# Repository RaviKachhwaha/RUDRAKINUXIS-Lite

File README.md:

<h1 align="center">
  <br>

  <br>
  RUDRAKINUXIS-Lite
  <br>
</h1>
<h3 align="center">
A fully open-sourced complete Field Oriented Control ESC. 
</h3>

| Front Render | Back Render | 
| --- | --- |
|  |  | 

## Schematics  

Here are the schematic design,

## Features
- **STM32G431CBU6 MCU** - Arm Cortex-M4 with CORDIC accelerator, running at 170 MHz.
- **A 24kHz 6S FOC motor controller and real-time DSP**.
- **Texas Instruments DRV8300 gate driver**.
- **600W continuous with 16 AWG bus wire and 2oz copper support**.
- Power and arming status indicator LEDs.
- High-speed CAN FD and DShot support.
- **USB C** - for flashing and telemetry.
- A 20-25.2V (6S LiPo) pad input for power.
- **3-phase 0.5mΩ low side shunts** - with dedicated Kelvin differential sensing.
- **LMR36510 synchronous buck converter** - high efficiency step down for the 10V gate rail.
- **AP2112K ultra low noise 3.3V LDO** - delivers clean, ripple free power to the MCU ADC.
- **Phase BEMF and bus voltage sensing** - for sensorless motor tracking and battery telemetry.
- **Onboard NTC thermistor** - for real time thermal monitoring and overheat protection.
- **USBLC6-2SC6 ESD protection** - hardware transient voltage clamping on USB data lines.
- **SWD debug header** - 5-pin port for direct ST-Link firmware flashing and live debugging.

## PCB Design 
|  |
|--- |  

 ### The PCB is 4 layers with dimensions 78.5000 x 55.0000 mm, made to be easily useable for anyone.  

 ### All the PCB files are [here](https://github.com/RaviKachhwaha/RUDRAKINUXIS-Lite/blob/main/hardware) 

| Front Layer | Inner Layer 1 |
| --- | --- |
|  |  |
| Inner Layer 2 | Bottom layer |
|  |  |

## Pinout  

This is a general pinout 

|  | 
| --- | 

Note :- Sorry, I am not able to create it's Pinout image due to storage issues in my PC, but I will create and upload pinout image as soon as possible.

(Credits to KiCad EDA for KiCad 10, STMicroelectronics for the STM32G4 MCU, Texas Instruments for the DRV8300 gate driver, and Hack Club for funding to make this possible.)

(Thanks to hack Club for funding.) 

## Why was it made?  

While using the normal old ESC for my many projects and in some times need's, I realised it doesn't have Field Oriented Control and high power support and I couldn't use it for high power and control needed project, unfortunately I had to think to buy a different high power ESC then I see that those have high power but not Field Oriented Control support or many have Field Oriented Control but cost very high and not have my needed pins and full control over every thing and use very low price components which give low quality, but now I designed one with the simplicity of STM32G431CBU6 with being able to get best Field Oriented Control and fastest processing and control over every thing and also programming support in a same board with high quality Field Oriented Control for best flight and have too many features and this will make many things possible.

## How you can get one for yourself? 

That is pretty easy, you have all the files you will need in the production folder, order the development  
board from any PCB fab ( I chose Lion Circuits or PCB Power cause its cheap in India and has good quality and also made in India ) and BINGO! You will have it to use for any purpose you want!  

## How do you use it?  
You can use it as any normal ESC board but first want to flash the firmware which is given in firmware folder, for flashing first connect the ESC to your computer via USB-C. Open your flashing tool (STM32CubeProgrammer or stm32flash), select the CP2102N COM port, and click **Download / Flash**. The onboard auto-reset circuit automatically enters the STM32 system bootloader, flashes the binary, and boots directly into your firmware and you are good to go!
I have attached a simple firmware to start with prebuild firmware available in the firmware folder.  

## BOM  
|Name|Purpose          |Quantity|Total Cost (USD)|Link               |Distributor|
|----|-----------------|--------|----------------|-------------------|-----------|
|PCBA|Board and Assembly|4       |194.20         |[Lion Circuits](lioncircuits.com)|Lion Circuits     |
|Electronic Components|BOM Component Sourcing|4       |189.85           |[Lion Circuits](lioncircuits.com)|Lion Circuits     |
|GenX Lithium Ion Battery - 6S|Lithium Ion Battery - 21.6V 9000mAh and 13C is needed to test this ESC without this there is no option to test it. So this is must needed.|1       |111.11          |[GenX Lithium Ion Battery](https://genxbattery.com/shop/genx-molicel-21-6v-9000mah-13c-premium-lithium-ion-rechargeable-battery)|GenX     |
| | | Total | 495.16 |

LCSC & DigiKey BOM for the components on board is [here](https://github.com/RaviKachhwaha/RUDRAKINUXIS-Lite/blob/main/components_bom.csv)

!!Thanks to ALL!!

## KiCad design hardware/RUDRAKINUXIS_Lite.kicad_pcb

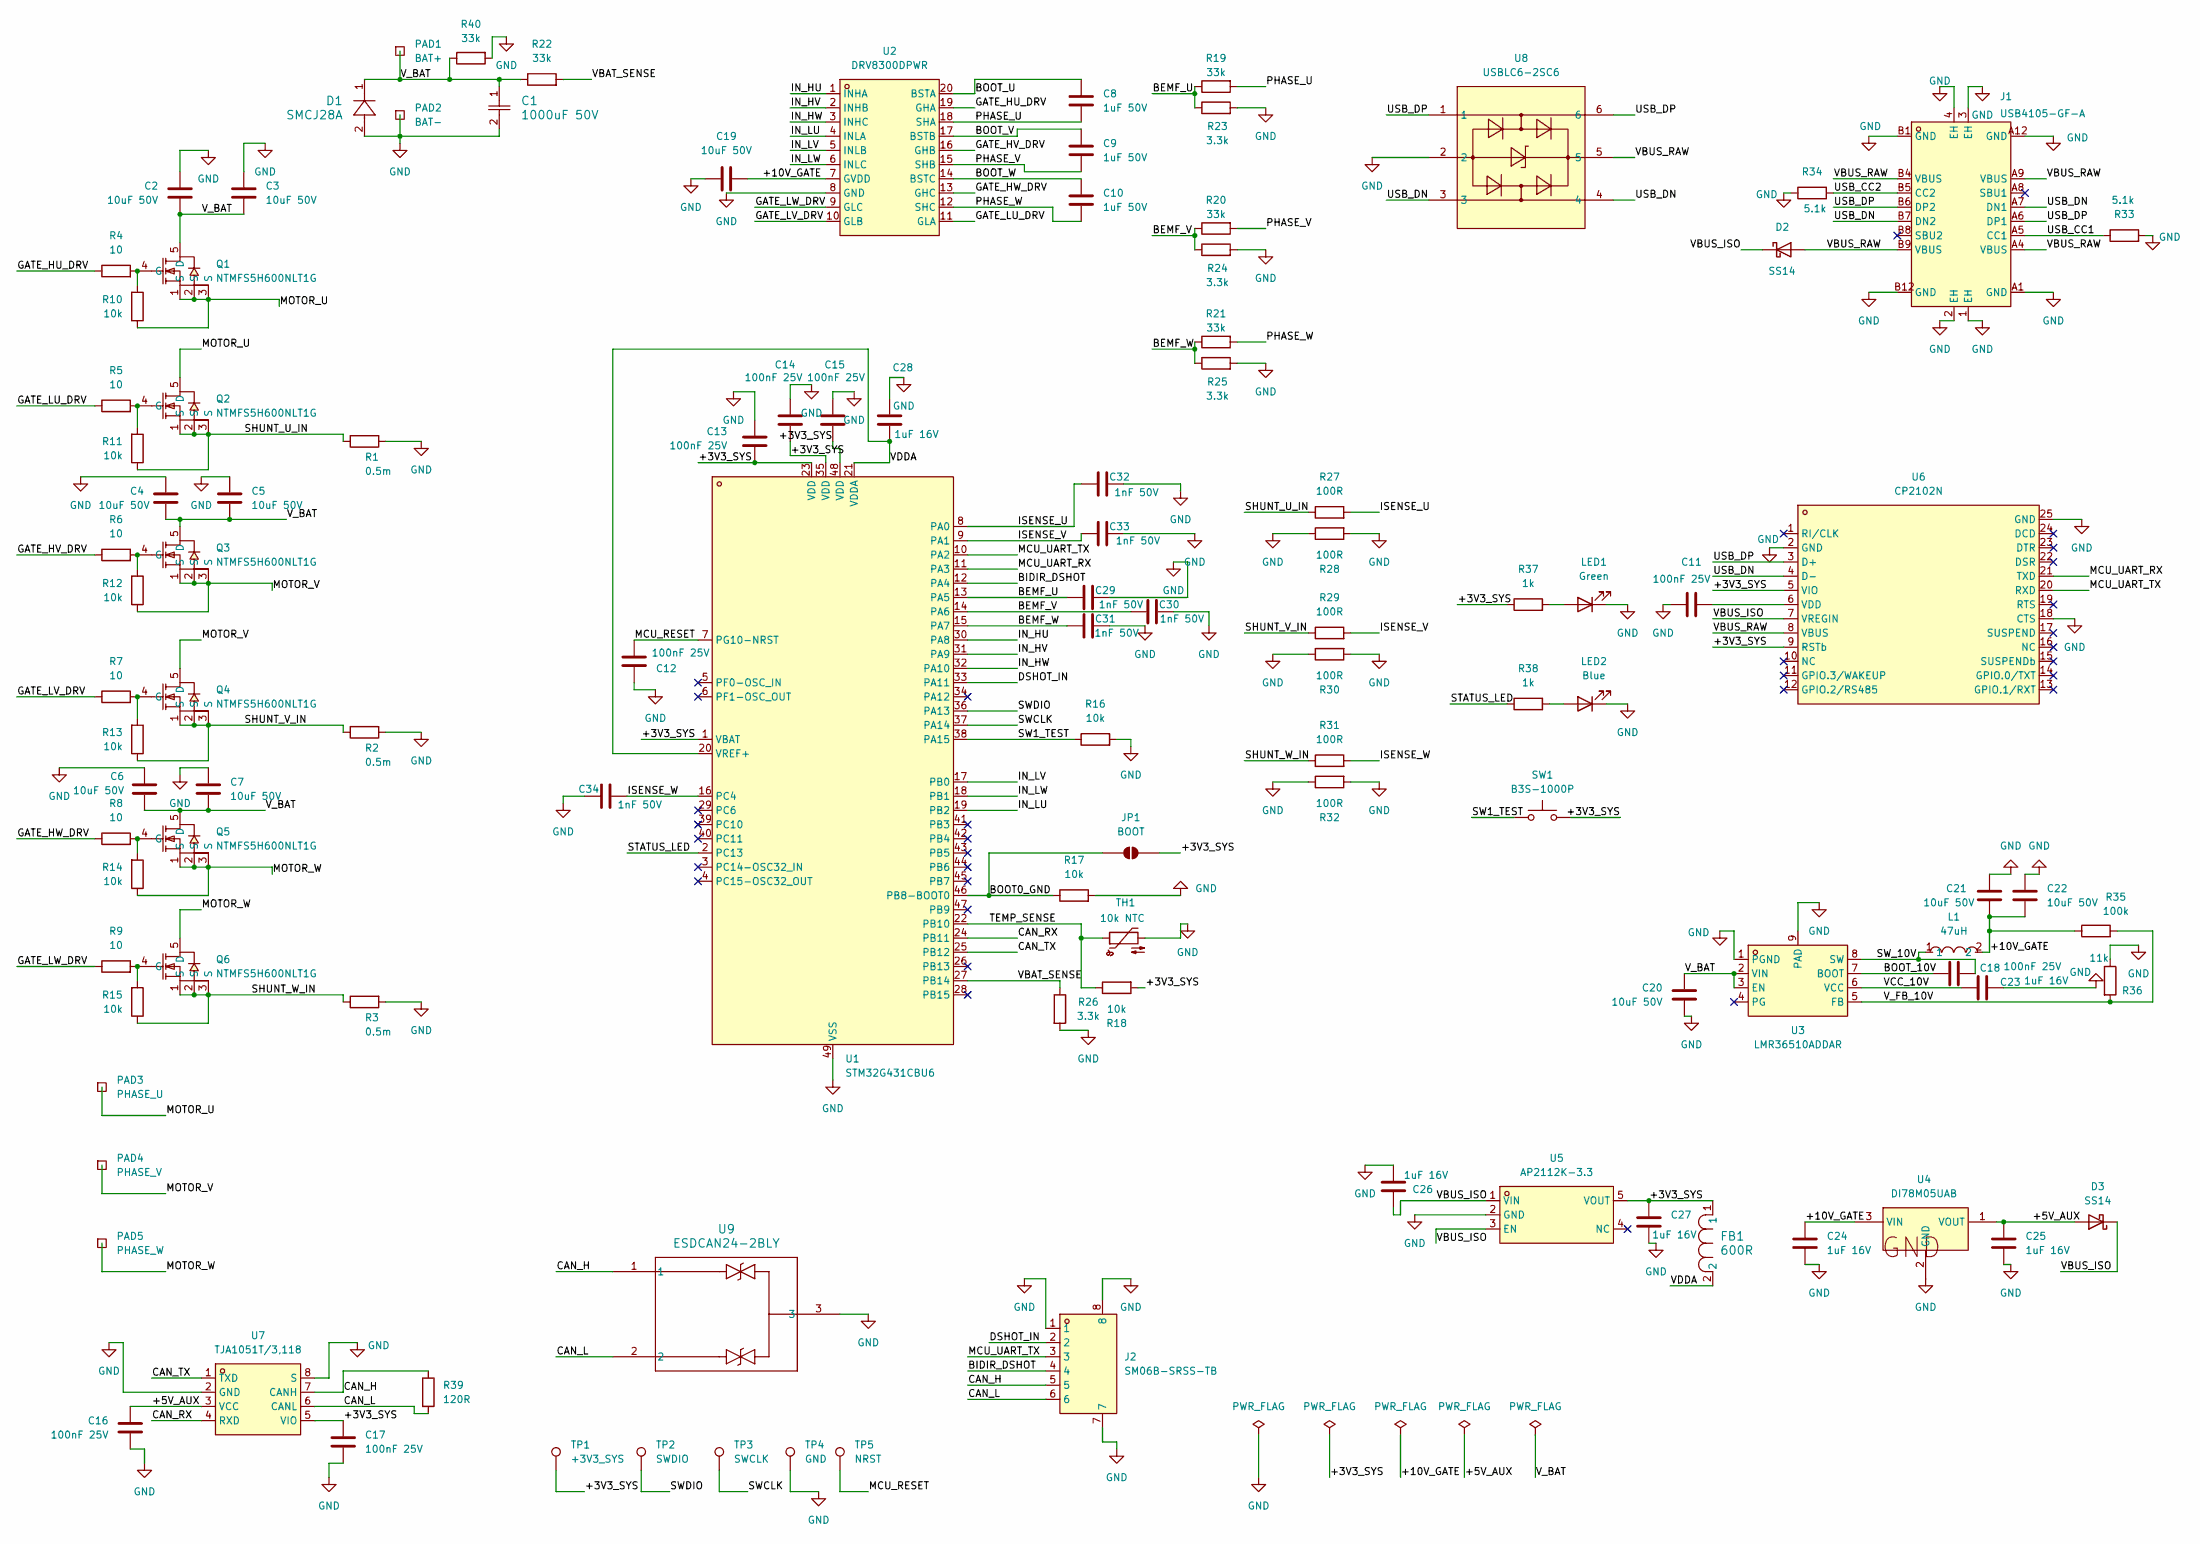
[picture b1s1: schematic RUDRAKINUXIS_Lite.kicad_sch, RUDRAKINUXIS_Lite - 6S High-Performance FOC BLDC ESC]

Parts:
C1: 1000uF 50V; CAP_16 X 25_PAN
C2, C3, C4, C5, C6, C7, C19, C20, C21, C22: 10uF 50V; C_1206_3216Metric
C8, C9, C10: 1uF 50V; C_0603_1608Metric
C11, C12, C13, C14, C15, C16, C17, C18: 100nF 25V; C_0603_1608Metric
C23, C24, C25, C26, C27, C28: 1uF 16V; C_0603_1608Metric
C29, C30, C31, C32, C33, C34: 1nF 50V; C_0603_1608Metric
D1: SMCJ28A; DIODE_DO-214AC
D2, D3: SS14; D_SMA
FB1: 600R; L_0603_1608Metric
J1: USB4105-GF-A; TYPE-C-SMD_SBC-160S1A-20-S412; MPN USB4105-GF-A; LCSC Part C3020560
J2: SM06B-SRSS-TB; CONN-SMD_SM06B-SRSS-TB-LF-SN; MPN SM06B-SRSS-TB(LF)(SN); LCSC Part C160405
JP1: BOOT; SolderJumper-2_P1.3mm_Open_RoundedPad1.0x1.5mm
L1: 47uH; IND-SMD_L10.2-W10.0; MPN CDRH105RNP-470NC; LCSC Part C225032
LED1: Green; LED_0603_1608Metric
LED2: Blue; LED_0603_1608Metric
PAD1: BAT+; TestPoint_THTPad_4.0x4.0mm_Drill2.0mm
PAD2: BAT-; TestPoint_THTPad_4.0x4.0mm_Drill2.0mm
PAD3: PHASE_U; TestPoint_THTPad_4.0x4.0mm_Drill2.0mm
PAD4: PHASE_V; TestPoint_THTPad_4.0x4.0mm_Drill2.0mm
PAD5: PHASE_W; TestPoint_THTPad_4.0x4.0mm_Drill2.0mm
Q1, Q2, Q3, Q4, Q5, Q6: NTMFS5H600NLT1G; DFN-5_L5.9-W4.9-P1.27-LS6.2-BL_CASE-488AA; MPN NTMFS5H600NLT1G; LCSC Part C463882
R1, R2, R3: 0.5m; R_2512_6332Metric
R4, R5, R6, R7, R8, R9: 10; R_0603_1608Metric
R10, R11, R12, R13, R14, R15, R16, R17, R18: 10k; R_0603_1608Metric
R19, R20, R21, R22: 33k; R_0603_1608Metric
R23, R24, R25, R26: 3.3k; R_0603_1608Metric
R27, R28, R29, R30, R31, R32: 100R; R_0603_1608Metric
R33, R34: 5.1k; R_0603_1608Metric
R35: 100k; R_0603_1608Metric
R36: 11k; R_0603_1608Metric
R37, R38: 1k; R_0603_1608Metric
R39: 120R; R_0805_2012Metric
R40: 33k; R_1206_3216Metric
SW1: B3S-1000P; SW_SPST_B3S-1000
TH1: 10k NTC; R_0603_1608Metric
TP1: +3V3_SYS; TestPoint_THTPad_2.0x2.0mm_Drill1.0mm
TP2: SWDIO; TestPoint_THTPad_2.0x2.0mm_Drill1.0mm
TP3: SWCLK; TestPoint_THTPad_2.0x2.0mm_Drill1.0mm
TP4: GND; TestPoint_THTPad_2.0x2.0mm_Drill1.0mm
TP5: NRST; TestPoint_THTPad_2.0x2.0mm_Drill1.0mm
U1: STM32G431CBU6; VQFN-48_L7.0-W7.0-P0.50-BL-EP5.5; MPN STM32G431CBU6; LCSC Part C529356
U2: DRV8300DPWR; TSSOP-20_L6.5-W4.4-P0.65-LS6.4-BL; MPN DRV8300DPWR; LCSC Part C3036056
U3: LMR36510ADDAR; SOP-8_L5.0-W4.0-P1.27-LS6.2-BL-EP; MPN LMR36510ADDAR; LCSC Part C1858393
U4: DI78M05UAB; SOT-89-3_L4.5-W2.5-P1.50-LS4.2-TL; MPN L78L05ABUTR; LCSC Part C42738
U5: AP2112K-3.3; SOT-25-5_L2.9-W1.6-P0.95-LS2.8-BL; MPN AP2112K-3.3TRG1; LCSC Part C51118
U6: CP2102N; QFN-24_L4.0-W4.0-P0.50-TL-EP2.6; MPN CP2102N-A02-GQFN24R; LCSC Part C969151
U7: TJA1051T/3,118; SOIC-8_L4.9-W3.9-P1.27-LS6.0-BL; MPN TJA1051T/3,118; LCSC Part C58988
U8: USBLC6-2SC6; SOT-23-6_L2.9-W1.6-P0.95-LS2.8-BL; MPN USBLC6-2SC6; LCSC Part C7519
U9: ESDCAN24-2BLY; SOT_24-2BLY_STM

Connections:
/+3V3_SYS: C13.1, C14.1, C15.1, C17.2, C27.1, FB1.1, JP1.2 (B), R18.2, R37.1, SW1.1, TP1.1 (1_1), U1.1 (VBAT), U1.23 (VDD), U1.35 (VDD), U1.48 (VDD), U5.5 (VOUT), U6.5 (VIO), U6.9 (RSTb), U7.5 (VIO)
/+5V_AUX: C16.2, C25.1, D3.2 (A), U4.1 (VOUT), U7.3 (VCC)
/+10V_GATE: C19.2, C21.2, C22.2, C24.1, L1.2, R35.1, U2.7 (GVDD), U4.3 (VIN)
/BEMF_U: C29.1, R19.1, R23.1, U1.13 (PA5)
/BEMF_V: C30.1, R20.1, R24.1, U1.14 (PA6)
/BEMF_W: C31.1, R21.1, R25.1, U1.15 (PA7)
/BIDIR_DSHOT: J2.4, U1.12 (PA4)
/BOOT0_GND: JP1.1 (A), R17.1, U1.46 (PB8-BOOT0)
/BOOT_10V: C18.2, U3.7 (BOOT)
/BOOT_U: C8.2, U2.20 (BSTA)
/BOOT_V: C9.2, U2.17 (BSTB)
/BOOT_W: C10.2, U2.14 (BSTC)
/CAN_H: J2.5, R39.1, U7.7 (CANH), U9.1
/CAN_L: J2.6, R39.2, U7.6 (CANL), U9.2
/CAN_RX: U1.24 (PB11), U7.4 (RXD)
/CAN_TX: U1.25 (PB12), U7.1 (TXD)
/DSHOT_IN: J2.2, U1.33 (PA11)
/GATE_HU_DRV: R4.1, U2.19 (GHA)
/GATE_HV_DRV: R6.1, U2.16 (GHB)
/GATE_HW_DRV: R8.1, U2.13 (GHC)
/GATE_LU_DRV: R5.1, U2.11 (GLA)
/GATE_LV_DRV: R7.1, U2.10 (GLB)
/GATE_LW_DRV: R9.1, U2.9 (GLC)
/IN_HU: U1.30 (PA8), U2.1 (INHA)
/IN_HV: U1.31 (PA9), U2.2 (INHB)
/IN_HW: U1.32 (PA10), U2.3 (INHC)
/IN_LU: U1.19 (PB2), U2.4 (INLA)
/IN_LV: U1.17 (PB0), U2.5 (INLB)
/IN_LW: U1.18 (PB1), U2.6 (INLC)
/ISENSE_U: C32.1, R27.2, U1.8 (PA0)
/ISENSE_V: C33.1, R29.2, U1.9 (PA1)
/ISENSE_W: C34.1, R31.2, U1.16 (PC4)
/MCU_RESET: C12.1, TP5.1 (1_1), U1.7 (PG10-NRST)
/MCU_UART_RX: U1.11 (PA3), U6.21 (TXD)
/MCU_UART_TX: J2.3, U1.10 (PA2), U6.20 (RXD)
/MOTOR_U: PAD3.1 (1_1), Q1.1 (S), Q1.2 (S), Q1.3 (S), Q2.5 (D), R10.1
/MOTOR_V: PAD4.1 (1_1), Q3.1 (S), Q3.2 (S), Q3.3 (S), Q4.5 (D), R12.1
/MOTOR_W: PAD5.1 (1_1), Q5.1 (S), Q5.2 (S), Q5.3 (S), Q6.5 (D), R14.1
/PHASE_U: C8.1, R19.2, U2.18 (SHA)
/PHASE_V: C9.1, R20.2, U2.15 (SHB)
/PHASE_W: C10.1, R21.2, U2.12 (SHC)
/SHUNT_U_IN: Q2.1 (S), Q2.2 (S), Q2.3 (S), R1.1, R11.1, R27.1
/SHUNT_V_IN: Q4.1 (S), Q4.2 (S), Q4.3 (S), R2.1, R13.1, R29.1
/SHUNT_W_IN: Q6.1 (S), Q6.2 (S), Q6.3 (S), R3.1, R15.1, R31.1
/STATUS_LED: R38.1, U1.2 (PC13)
/SW1_TEST: R16.1, SW1.2, U1.38 (PA15)
/SWCLK: TP3.1 (1_1), U1.37 (PA14)
/SWDIO: TP2.1 (1_1), U1.36 (PA13)
/SW_10V: C18.1, L1.1, U3.8 (SW)
/TEMP_SENSE: R18.1, TH1.1, U1.22 (PB10)
/USB_CC1: J1.A5 (CC1), R33.1
/USB_CC2: J1.B5 (CC2), R34.2
/USB_DN: J1.A7 (DN1), J1.B7 (DN2), U6.4 (D-), U8.3, U8.4
/USB_DP: J1.A6 (DP1), J1.B6 (DP2), U6.3 (D+), U8.1, U8.6
/VBAT_SENSE: R22.2, R26.1, U1.27 (PB14)
/VBUS_ISO: C26.1, D2.1 (K), D3.1 (K), U5.1 (VIN), U5.3 (EN), U6.7 (VREGIN)
/VBUS_RAW: D2.2 (A), J1.A4 (VBUS), J1.A9 (VBUS), J1.B4 (VBUS), J1.B9 (VBUS), U6.8 (VBUS), U8.5
/VCC_10V: C23.2, U3.6 (VCC)
/VDDA: C28.2, FB1.2, U1.20 (VREF+), U1.21 (VDDA)
/V_BAT: C1.1, C2.2, C3.2, C4.2, C5.2, C6.2, C7.2, C20.1, D1.1, PAD1.1 (1_1), Q1.5 (D), Q3.5 (D), Q5.5 (D), R22.1, R40.1, U3.2 (VIN), U3.3 (EN)
/V_FB_10V: R35.2, R36.2, U3.5 (FB)
GND: C1.2, C2.1, C3.1, C4.1, C5.1, C6.1, C7.1, C11.1, C12.2, C13.2, C14.2, C15.2, C16.1, C17.1, C19.1, C20.2, C21.1, C22.1, C23.1, C24.2, C25.2, C26.2, C27.2, C28.1, C29.2, C30.2, C31.2, C32.2, C33.2, C34.2, D1.2, J1.1 (EH), J1.2 (EH), J1.3 (EH), J1.4 (EH), J1.A1 (GND), J1.A12 (GND), J1.B1 (GND), J1.B12 (GND), J2.1, J2.7, J2.8, LED1.1 (K), LED2.1 (K), PAD2.1 (1_1), R1.2, R2.2, R3.2, R16.2, R17.2, R23.2, R24.2, R25.2, R26.2, R28.1, R28.2, R30.1, R30.2, R32.1, R32.2, R33.2, R34.1, R36.1, R40.2, TH1.2, TP4.1 (1_1), U1.49 (VSS), U2.8 (GND), U3.1 (PGND), U3.9 (PAD), U4.2 (GND), U5.2 (GND), U6.2 (GND), U6.18 (CTS), U6.25 (GND), U7.2 (GND), U7.8 (S), U8.2, U9.3
unnamed: LED1.2 (A), R37.2
unnamed: LED2.2 (A), R38.2
unnamed: Q1.4 (G), R4.2, R10.2
unnamed: Q2.4 (G), R5.2, R11.2
unnamed: Q3.4 (G), R6.2, R12.2
unnamed: Q4.4 (G), R7.2, R13.2
unnamed: Q5.4 (G), R8.2, R14.2
unnamed: Q6.4 (G), R9.2, R15.2
unnamed: C11.2, U6.6 (VDD)

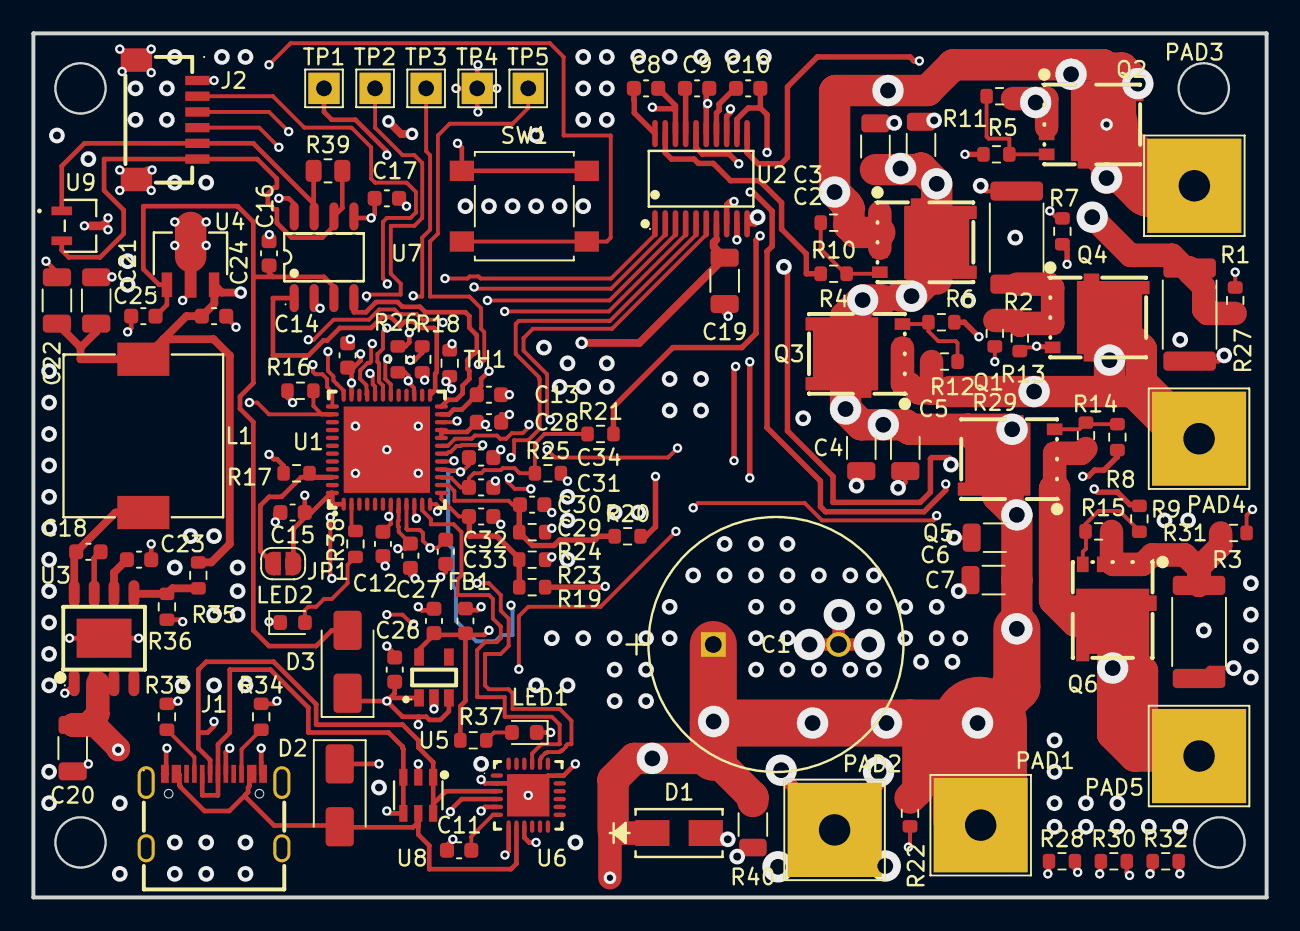
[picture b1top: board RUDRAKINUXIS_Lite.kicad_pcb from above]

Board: 4 copper layers, 78.5 x 55.0 mm, 111 parts (0 on the bottom side), 71 nets.

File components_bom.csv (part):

Item #,Reference,Qty,Value,Description,Footprint,Manufacturer,MPN,LCSC Part,Unit Price (₹),Unit Price ($),Total Price (₹),Total Price ($),Supplier Link
1,U1,1,STM32G431CBU6,"170MHz ARM Cortex-M4F MCU, Hardware CORDIC, Math Accelerator, Dual 12-Bit ADC, UFQFPN-48",easyeda2kicad:STM32G431CBU6,STMicroelectronics,STM32G431CBU6,C529356,435.50,4.85,435.50,4.85,https://www.lcsc.com/product-detail/C529356.html
2,U2,1,DRV8300DPWR,"High-Current 100V 3-Phase Gate Driver, 750mA Source / 1500mA Sink, Integrated Bootstrap Diodes, TSSOP-20",easyeda2kicad:DRV8300DPWR,Texas Instruments,DRV8300DPWR,C3036056,195.00,2.15,195.00,2.15,https://www.lcsc.com/product-detail/C3036056.html
3,U3,1,LMR36510ADDAR,Wide-Input 65V 1A Synchronous Step-Down Buck Regulator for 10.0V Gate Drive Rail,easyeda2kicad:LMR36510ADDAR,Texas Instruments,LMR36510ADDAR,C1858393,165.00,1.82,165.00,1.82,https://www.lcsc.com/product-detail/C1858393.html
4,U4,1,L78L05ABUTR,5.0V 100mA Linear Voltage Regulator for CAN Transceiver VCC Supply Rail,easyeda2kicad:L78L05ABUTR,STMicroelectronics,L78L05ABUTR,C42738,24.50,0.27,24.50,0.27,https://www.lcsc.com/product-detail/C42738.html
5,U5,1,AP2112K-3.3TRG1,"3.3V 600mA Ultra-Low-Noise CMOS LDO Regulator for MCU, Logic & Analog Rails, SOT-23-5",easyeda2kicad:AP2112K-3.3TRG1,Diodes Incorporated,AP2112K-3.3TRG1,C51118,28.00,0.31,28.00,0.31,https://www.lcsc.com/product-detail/C51118.html
6,U6,1,CP2102N-A02-GQFN24R,USB 2.0 Full-Speed to UART Bridge Controller with Integrated Clock & Oscillator,easyeda2kicad:CP2102N-A02-GQFN24R,Silicon Labs,CP2102N-A02-GQFN24R,C969151,185.00,2.05,185.00,2.05,https://www.lcsc.com/product-detail/C969151.html
7,U7,1,"TJA1051T/3,118",High-Speed CAN FD Transceiver with 3.3V Microcontroller Logic IO Interface,Package_SO:SOIC-8_3.9x4.9mm_P1.27mm,NXP Semiconductors,"TJA1051T/3,118",C58988,62.00,0.68,62.00,0.68,https://www.lcsc.com/product-detail/C58988.html
8,U8,1,USBLC6-2SC6,Ultra-Low Capacitance (0.25pF) Dual-Line High-Speed USB 2.0 ESD Protection Array,Package_TO_SOT_SMD:SOT-23-6,STMicroelectronics,USBLC6-2SC6,C7519,18.50,0.20,18.50,0.20,https://www.lcsc.com/product-detail/C7519.html
9,U9,1,ESDCAN24-2BLY,Dual Automotive-Grade CAN Bus Transient Surge & ESD Clamping Diode Array 24V,Package_TO_SOT_SMD:SOT-23,STMicroelectronics,ESDCAN24-2BLY,C2836262,22.00,0.24,22.00,0.24,https://www.lcsc.com/product-detail/C2836262.html
10,"Q1, Q2, Q3, Q4, Q5, Q6",6,NTMFS5H600NL,"60V 1.3mOhm N-Channel Power MOSFET, 198A, Logic-Level Gate Drive, DFN-5 (5x6mm) / SO-8FL",easyeda2kicad:NTMFS5H600NLT1G,onsemi,NTMFS5H600NLT1G,C463882,145.00,1.60,870.00,9.60,https://www.lcsc.com/product-detail/C463882.html
11,D1,1,SMCJ28A,"1500W Peak Pulse Power Unidirectional TVS Diode, 28V Standoff, 45.4V Max Clamp, DO-214AB (SMC)",Diode_SMD:D_SMC,Bourns Inc.,SMCJ28A,C2833130,38.00,0.42,38.00,0.42,https://www.lcsc.com/product-detail/C2833130.html
12,"D2, D3",2,SS14,40V 1A Low Forward Drop Surface Mount Schottky Barrier Rectifier Diode,Diode_SMD:D_SMA,Vishay Semiconductor,SS14-E3/61T,C88863,12.00,0.13,24.00,0.26,https://www.lcsc.com/product-detail/C88863.html
13,J1,1,USB4105-GF-A,16-Pin SMT USB Type-C Receptacle Port with Through-Hole Shell Shield Anchors,easyeda2kicad:USB4105-GF-A,Global Connector Technology (GCT),USB4105-GF-A,C3020560,76.50,0.85,76.50,0.85,https://www.lcsc.com/product-detail/C3020560.html
14,J2,1,SM06B-SRSS-TB,"6-Pin 1.0mm Pitch Shrouded Header for Flight Controller Interface (DroneCAN/DShot), 1.0mm SMD",easyeda2kicad:SM06B-SRSS-TB_LF__SN_,JST,SM06B-SRSS-TB(LF)(SN),C160405,28.50,0.31,28.50,0.31,https://www.lcsc.com/product-detail/C160405.html
15,SW1,1,B3S-1000P,6.0x3.5mm Surface Mount Tactile Pushbutton (Hardware Autonomous Bench Test Mode),easyeda2kicad:B3S-1000P,Omron Electronics,B3S-1000P,C180420,36.00,0.40,36.00,0.40,https://www.lcsc.com/product-detail/C180420.html
16,L1,1,47uH 2A,47uH 2A Shielded Power Inductor for LMR36510 10V Synchronous Buck Rail,easyeda2kicad:CDRH105RNP-470NC,Sumida America,CDRH105RNP-470NC,C225032,65.00,0.72,65.00,0.72,https://www.lcsc.com/product-detail/C225032.html
17,FB1,1,600R 1A,Ferrite Bead 600 Ohm @ 100MHz 1A 0.15R DCR for Isolated VDDA Analog Rail Island 0603,Inductor_SMD:L_0603_1608Metric,Murata Manufacturing,BLM18KG601SN1D,C1015,14.00,0.15,14.00,0.15,https://www.lcsc.com/product-detail/C1015.html
18,TH1,1,10k NTC 1%,10k Ohm NTC Thermistor 1% Beta=3380K for Inverter Bridge Temperature Monitoring 0603,Resistor_SMD:R_0603_1608Metric,Murata Manufacturing,NCU18XH103J60RB,C25804,16.00,0.18,16.00,0.18,https://www.lcsc.com/product-detail/C25804.html
19,LED1,1,Green LED,Green Surface Mount SMD LED 568nm (3.3V Power Rail Active Indicator) 0603,LED_SMD:LED_0603_1608Metric,Kingbright,APT1608SGC,C84268,12.50,0.14,12.50,0.14,https://www.lcsc.com/product-detail/C84268.html
20,LED2,1,Blue LED,Blue Surface Mount SMD LED 470nm (ESC Armed / Status & Fault Diagnostic Indicator) 0603,LED_SMD:LED_0603_1608Metric,Kingbright,APT1608QBC/D,C84269,16.50,0.18,16.50,0.18,https://www.lcsc.com/product-detail/C84269.html
21,"R1, R2, R3",3,0.5m 5W 1%,"0.0005 Ohm (0.5mR) 5W 1% Metal Strip Kelvin Current Sensing Shunts, 2512 (6332 Metric)",Resistor_SMD:R_2512_6332Metric,Delta Electronics / Cyntec,SCMM2512S5-0M50F,C3142273,88.00,0.97,264.00,2.91,https://www.lcsc.com/product-detail/C3142273.html
22,"R4, R5, R6, R7, R8, R9",6,10 1%,10 Ohm 1% 0.1W Thick Film Chip Resistor for MOSFET Gate Slew Damping 0603,Resistor_SMD:R_0603_1608Metric,YAGEO,RC0603FR-0710RL,C22775,2.50,0.027,15.00,0.16,https://www.lcsc.com/product-detail/C22775.html
23,"R10, R11, R12, R13, R14, R15, R16, R17, R18",9,10k 1%,"10k Ohm 1% 0.1W Thick Film Chip Resistor for Gate Bleeders, SW1 Pull-down, BOOT0, and NTC Bias 0603",Resistor_SMD:R_0603_1608Metric,YAGEO,RC0603FR-0710KL,C25804,2.50,0.027,22.50,0.24,https://www.lcsc.com/product-detail/C25804.html
24,"R19, R20, R21, R22",4,33k 1%,"33k Ohm 1% 0.1W Thick Film Chip Resistor for BEMF (Phase U, V, W) & VBAT High-Side Dividers 0603",Resistor_SMD:R_0603_1608Metric,YAGEO,RC0603FR-0733KL,C23145,2.50,0.027,10.00,0.11,https://www.lcsc.com/product-detail/C23145.html
25,"R23, R24, R25, R26",4,3.3k 1%,3.3k Ohm 1% 0.1W Thick Film Chip Resistor for BEMF & VBAT Low-Side Voltage Dividers 0603,Resistor_SMD:R_0603_1608Metric,YAGEO,RC0603FR-073K3L,C22978,2.50,0.027,10.00,0.11,https://www.lcsc.com/product-detail/C22978.html
26,"R27, R28, R29, R30, R31, R32",6,100R 1%,100 Ohm 1% 0.1W Thick Film Chip Resistor for Shunt Kelvin Differential RC Noise Filter 0603,Resistor_SMD:R_0603_1608Metric,YAGEO,RC0603FR-07100RL,C22775,2.50,0.027,15.00,0.16,https://www.lcsc.com/product-detail/C22775.html
27,"R33, R34",2,5.1k 1%,5.1k Ohm 1% 0.1W Thick Film Chip Resistor for USB Type-C CC1/CC2 Channel Configuration 0603,Resistor_SMD:R_0603_1608Metric,YAGEO,RC0603FR-075K1L,C23186,2.50,0.027,5.00,0.05,https://www.lcsc.com/product-detail/C23186.html
28,R35,1,100k 1%,100k Ohm 1% 0.1W Thick Film Chip Resistor for LMR36510 Buck Regulator Upper Feedback 0603,Resistor_SMD:R_0603_1608Metric,YAGEO,RC0603FR-07100KL,C25803,2.50,0.027,2.50,0.03,https://www.lcsc.com/product-detail/C25803.html
29,R36,1,11k 1%,"11.0k Ohm 1% 0.1W Thick Film Chip Resistor for LMR36510 Buck Regulator Lower Feedback (~10.1V Out) 0603",Resistor_SMD:R_0603_1608Metric,YAGEO,RC0603FR-0711KL,C22802,2.50,0.027,2.50,0.03,https://www.lcsc.com/product-detail/C22802.html
30,"R37, R38",2,1k 1%,"1k Ohm 1% 0.1W Thick Film Chip Resistor for Indicator LED Current Limiting (LED1, LED2) 0603",Resistor_SMD:R_0603_1608Metric,YAGEO,RC0603FR-071KL,C21190,2.50,0.027,5.00,0.05,https://www.lcsc.com/product-detail/C21190.html
31,R39,1,120R 1%,120 Ohm 1% 0.125W Thick Film Resistor for CAN Differential Bus Jumper-Selectable Termination 0805,Resistor_SMD:R_0805_2012Metric,YAGEO,RC0805FR-07120RL,C17462,3.00,0.033,3.00,0.03,https://www.lcsc.com/product-detail/C17462.html
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
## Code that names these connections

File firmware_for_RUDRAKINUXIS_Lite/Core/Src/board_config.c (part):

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  gpio_init.Pull = LL_GPIO_PULL_NO;
  LL_GPIO_Init(GPIOB, &gpio_init);

  /*--- 2. Gate Driver DRV8300 Enable Pin (PC13) ---*/
  DRV_ENABLE_LOW(); /* Start in disabled state */
  gpio_init.Pin = DRV_ENABLE_PIN;
  gpio_init.Mode = LL_GPIO_MODE_OUTPUT;
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  gpio_init.Pull = LL_GPIO_PULL_DOWN;
  LL_GPIO_Init(DRV_ENABLE_PORT, &gpio_init);

  /*--- 3. TIM1 Complementary PWM High-Side (PA8, PA9, PA10 - AF6) ---*/
  gpio_init.Pin = TIM1_CH1_PIN | TIM1_CH2_PIN | TIM1_CH3_PIN;
  gpio_init.Mode = LL_GPIO_MODE_ALTERNATE;
  gpio_init.Speed = LL_GPIO_SPEED_FREQ_VERY_HIGH;
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  gpio_init.Alternate = LL_GPIO_AF_6;
  LL_GPIO_Init(GPIOA, &gpio_init);

  /*--- 4. TIM1 Complementary PWM Low-Side (PB13, PB14 - AF6; PB15 - AF4) ---*/
  gpio_init.Pin = TIM1_CH1N_PIN | TIM1_CH2N_PIN;
  gpio_init.Alternate = LL_GPIO_AF_6;
  LL_GPIO_Init(GPIOB, &gpio_init);
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  gpio_init.Alternate = LL_GPIO_AF_4;
  LL_GPIO_Init(GPIOB, &gpio_init);

  /*--- 5. TIM1 Hardware Break Input (PB12 - AF6) ---*/
  gpio_init.Pin = TIM1_BKIN_PIN;
  gpio_init.Mode = LL_GPIO_MODE_ALTERNATE;
  gpio_init.Speed = LL_GPIO_SPEED_FREQ_VERY_HIGH;
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  LL_GPIO_Init(TIM1_BKIN_PORT, &gpio_init);

  /*--- 6. Analog Current Sensing Inputs for Internal OPAMPs ---*/
  /* OPAMP1_INP (PA1), OPAMP2_INP (PA7) */
  gpio_init.Pin = OPAMP1_INP_PIN | OPAMP2_INP_PIN;
  gpio_init.Mode = LL_GPIO_MODE_ANALOG;
  gpio_init.Pull = LL_GPIO_PULL_NO;
  LL_GPIO_Init(GPIOA, &gpio_init);

  /* OPAMP3_INP (PB0) */
  gpio_init.Pin = OPAMP3_INP_PIN;
  LL_GPIO_Init(GPIOB, &gpio_init);

  /*--- 7. Analog Regular Sensing Channels (VBUS, BEMF_U/V/W, NTC) ---*/
  /* VBUS (PA0), NTC (PA4) */
  gpio_init.Pin = VBUS_ADC_PIN | NTC_ADC_PIN;
  gpio_init.Mode = LL_GPIO_MODE_ANALOG;
  gpio_init.Pull = LL_GPIO_PULL_NO;
  LL_GPIO_Init(GPIOA, &gpio_init);

  /* BEMF_U (PB2), BEMF_V (PB11) */
  gpio_init.Pin = BEMF_U_ADC_PIN | BEMF_V_ADC_PIN;
  LL_GPIO_Init(GPIOB, &gpio_init);

  /* BEMF_W (PC4) */
  gpio_init.Pin = BEMF_W_ADC_PIN;
  LL_GPIO_Init(GPIOC, &gpio_init);

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  gpio_init.Alternate = CLI_USART_TX_AF;
  LL_GPIO_Init(GPIOB, &gpio_init);

  /*--- 9. CAN FD Transceiver (PB8 RX, PB9 TX - AF9) ---*/
  gpio_init.Pin = CANFD_RX_PIN | CANFD_TX_PIN;
  gpio_init.Mode = LL_GPIO_MODE_ALTERNATE;
  gpio_init.Speed = LL_GPIO_SPEED_FREQ_VERY_HIGH;
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  gpio_init.Alternate = CANFD_RX_AF;
  LL_GPIO_Init(GPIOB, &gpio_init);

  /*--- 10. Flight Controller DShot / PWM Input (PA15 - AF1, TIM2_CH1) ---*/
  gpio_init.Pin = DSHOT_INPUT_PIN;
  gpio_init.Mode = LL_GPIO_MODE_ALTERNATE;
  gpio_init.Speed = LL_GPIO_SPEED_FREQ_VERY_HIGH;
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  LL_GPIO_Init(GPIOA, &gpio_init);

  /*--- 11. 5-Pin SWD Programming & Debug Interface (ST-Link V2 / V3) ---*/
  /* SWDIO (PA13) and SWCLK (PA14) are preserved in their default AF0 (SWD) state.
   * Pin 7 is hardware NRST (System Reset) with internal pull-up filter.
   * Both PA13 and PA14 are strictly protected and never repurposed as standard GPIOs,
   * guaranteeing reliable SWD flashing and full "Connect Under Reset" recovery. */
}

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  LL_APB2_GRP1_EnableClock(LL_APB2_GRP1_PERIPH_SYSCFG);

  /*--- OPAMP1 (Phase U Current) ---*/
  /* Non-inverting input: VINP0 (PA1) */
  LL_OPAMP_SetInputNonInverting(OPAMP1, LL_OPAMP_INPUT_NONINVERT_IO0);
  /* Inverting input: Internal PGA connected to internal resistor ladder */
  LL_OPAMP_SetInputInverting(OPAMP1, LL_OPAMP_INPUT_INVERT_CONNECT_NO);
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  LL_OPAMP_Enable(OPAMP1);

  /*--- OPAMP2 (Phase V Current) ---*/
  /* Non-inverting input: VINP0 (PA7) */
  LL_OPAMP_SetInputNonInverting(OPAMP2, LL_OPAMP_INPUT_NONINVERT_IO0);
  LL_OPAMP_SetInputInverting(OPAMP2, LL_OPAMP_INPUT_INVERT_CONNECT_NO);
  LL_OPAMP_SetPGAGain(OPAMP2, LL_OPAMP_PGA_GAIN_16_OR_MINUS_15);
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  LL_OPAMP_Enable(OPAMP2);

  /*--- OPAMP3 (Phase W Current) ---*/
  /* Non-inverting input: VINP0 (PB0) */
  LL_OPAMP_SetInputNonInverting(OPAMP3, LL_OPAMP_INPUT_NONINVERT_IO0);
  LL_OPAMP_SetInputInverting(OPAMP3, LL_OPAMP_INPUT_INVERT_CONNECT_NO);
  LL_OPAMP_SetPGAGain(OPAMP3, LL_OPAMP_PGA_GAIN_16_OR_MINUS_15);
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
  /*
   * Configure ADC1 Regular Sequencer for DMA round-robin:
   * Rank 1: Channel 1 (PA0, VBUS)
   * Rank 2: Channel 12 (PB2, BEMF_U)
   * Rank 3: Channel 14 (PB11, BEMF_V)
   * Rank 4: Channel 5 (PC4, BEMF_W)
   * Rank 5: Channel 17 (PA4, NTC Thermistor)
   * Rank 6: Channel 18 (VREFINT internal)
   */
  LL_ADC_REG_SetSequencerLength(ADC1, LL_ADC_REG_SEQ_SCAN_ENABLE_6RANKS);
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

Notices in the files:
firmware_for_RUDRAKINUXIS_Lite/Core/Src/board_config.c:
Copyright (c) 2026 RUDRAKINUXIS Project.
All rights reserved.
